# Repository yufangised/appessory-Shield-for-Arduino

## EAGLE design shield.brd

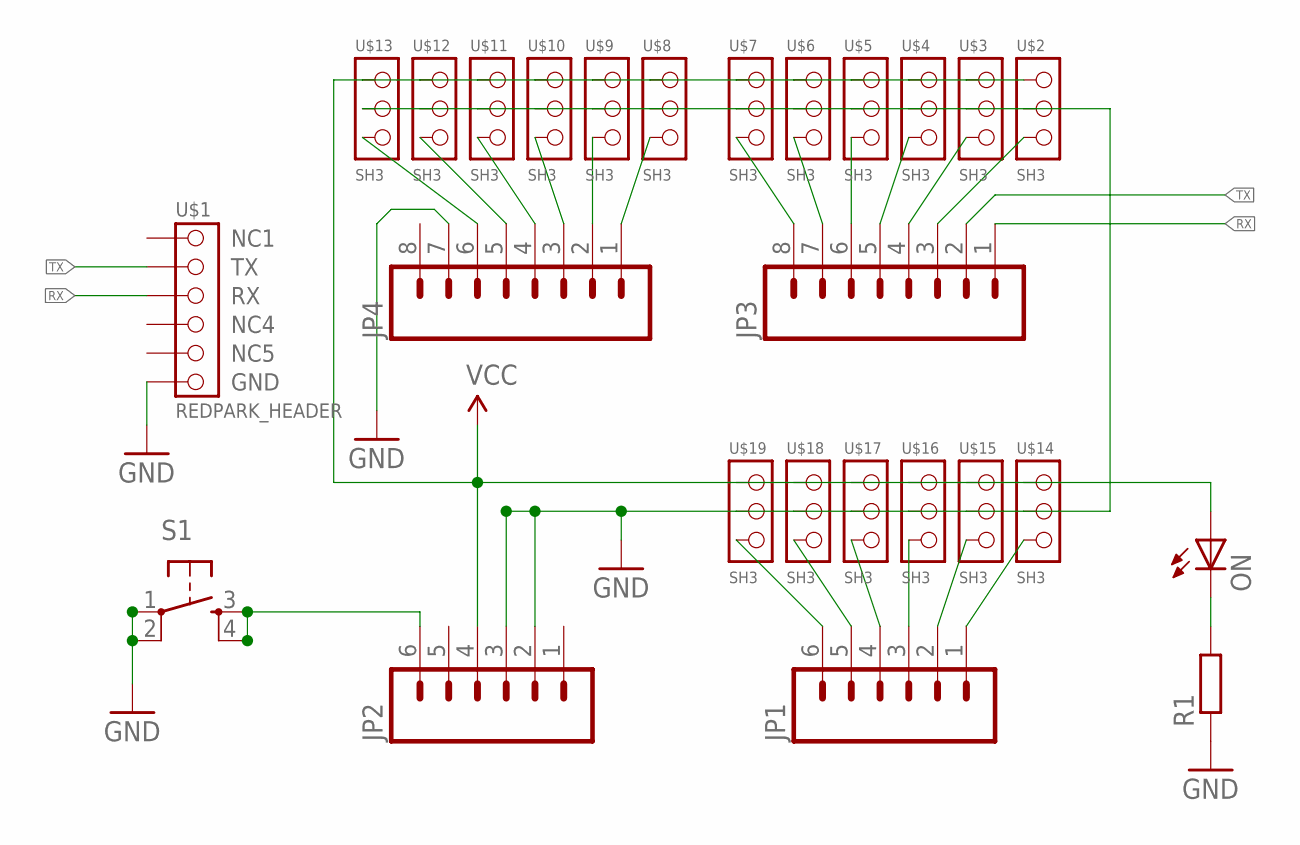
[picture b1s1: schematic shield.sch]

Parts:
JP1, JP2: M06SIP; 1X06
JP3, JP4: M081X08; 1X08
ON: LEDCHIP-LED0805; CHIP-LED0805
R1: R-EU_M0805; M0805
S1: TAC_SWITCHPTH; TACTILE-PTH
U$1: REDPARK_HEADER
U$2, U$3, U$4, U$5, U$6, U$7, U$8, U$9, U$10, U$11, U$12, U$13, U$14, U$15, U$16, U$17, U$18, U$19: SH3

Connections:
A0: JP1.6, U$19.+ (3)
A1: JP1.5, U$18.+ (3)
A2: JP1.4, U$17.+ (3)
A3: JP1.3, U$16.+ (3)
A4: JP1.2, U$15.+ (3)
A5: JP1.1, U$14.+ (3)
GND: JP2.2, JP2.3, JP4.7, R1.1, S1.1, S1.2, U$1.6 (GND), U$2.- (2), U$3.- (2), U$4.- (2), U$5.- (2), U$6.- (2), U$7.- (2), U$8.- (2), U$9.- (2), U$10.- (2), U$11.- (2), U$12.- (2), U$13.- (2), U$14.- (2), U$15.- (2), U$16.- (2), U$17.- (2), U$18.- (2), U$19.- (2)
IO2: JP3.3, U$2.+ (3)
IO3: JP3.4, U$3.+ (3)
IO4: JP3.5, U$4.+ (3)
IO5: JP3.6, U$5.+ (3)
IO6: JP3.7, U$6.+ (3)
IO7: JP3.8, U$7.+ (3)
IO8: JP4.1, U$8.+ (3)
IO9: JP4.2, U$9.+ (3)
IO10: JP4.3, U$10.+ (3)
IO11: JP4.4, U$11.+ (3)
IO12: JP4.5, U$12.+ (3)
IO13: JP4.6, U$13.+ (3)
unnamed: JP2.6, S1.3, S1.4
unnamed: ON.C, R1.2
RX: JP3.1, U$1.3 (RX)
TX: JP3.2, U$1.2 (TX)
VCC: JP2.4, ON.A, U$2.S (1), U$3.S (1), U$4.S (1), U$5.S (1), U$6.S (1), U$7.S (1), U$8.S (1), U$9.S (1), U$10.S (1), U$11.S (1), U$12.S (1), U$13.S (1), U$14.S (1), U$15.S (1), U$16.S (1), U$17.S (1), U$18.S (1), U$19.S (1)

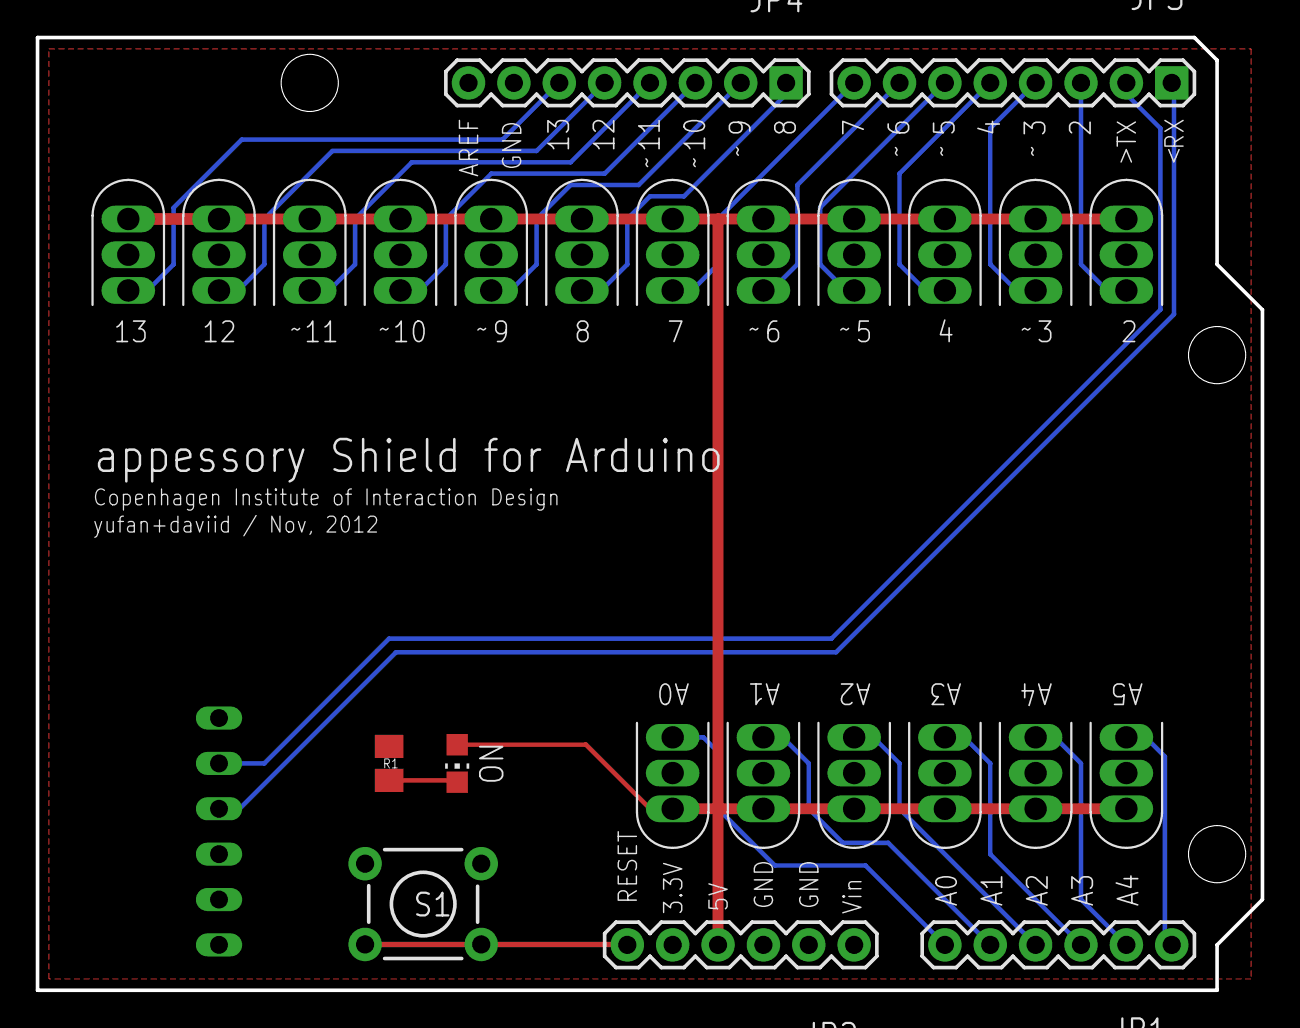
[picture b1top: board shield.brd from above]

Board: 2 copper layers, 68.6 x 53.3 mm, 45 parts (0 on the bottom side), 24 nets.

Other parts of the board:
U$20: ARDUINO-OUTLINE
U$21, U$22, U$23, U$24, U$25, U$26, U$27, U$28, U$29, U$30, U$31, U$32, U$33, U$34, U$35, U$36, U$37, U$38: CONNECTOR_OUTLINE

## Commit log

2012-11-29 apessory Shield for Arduino

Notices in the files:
parts and their libraries:
SparkFun: Licensing: CC v3.0 Share-Alike You are welcome to use this library for commercial purposes.
